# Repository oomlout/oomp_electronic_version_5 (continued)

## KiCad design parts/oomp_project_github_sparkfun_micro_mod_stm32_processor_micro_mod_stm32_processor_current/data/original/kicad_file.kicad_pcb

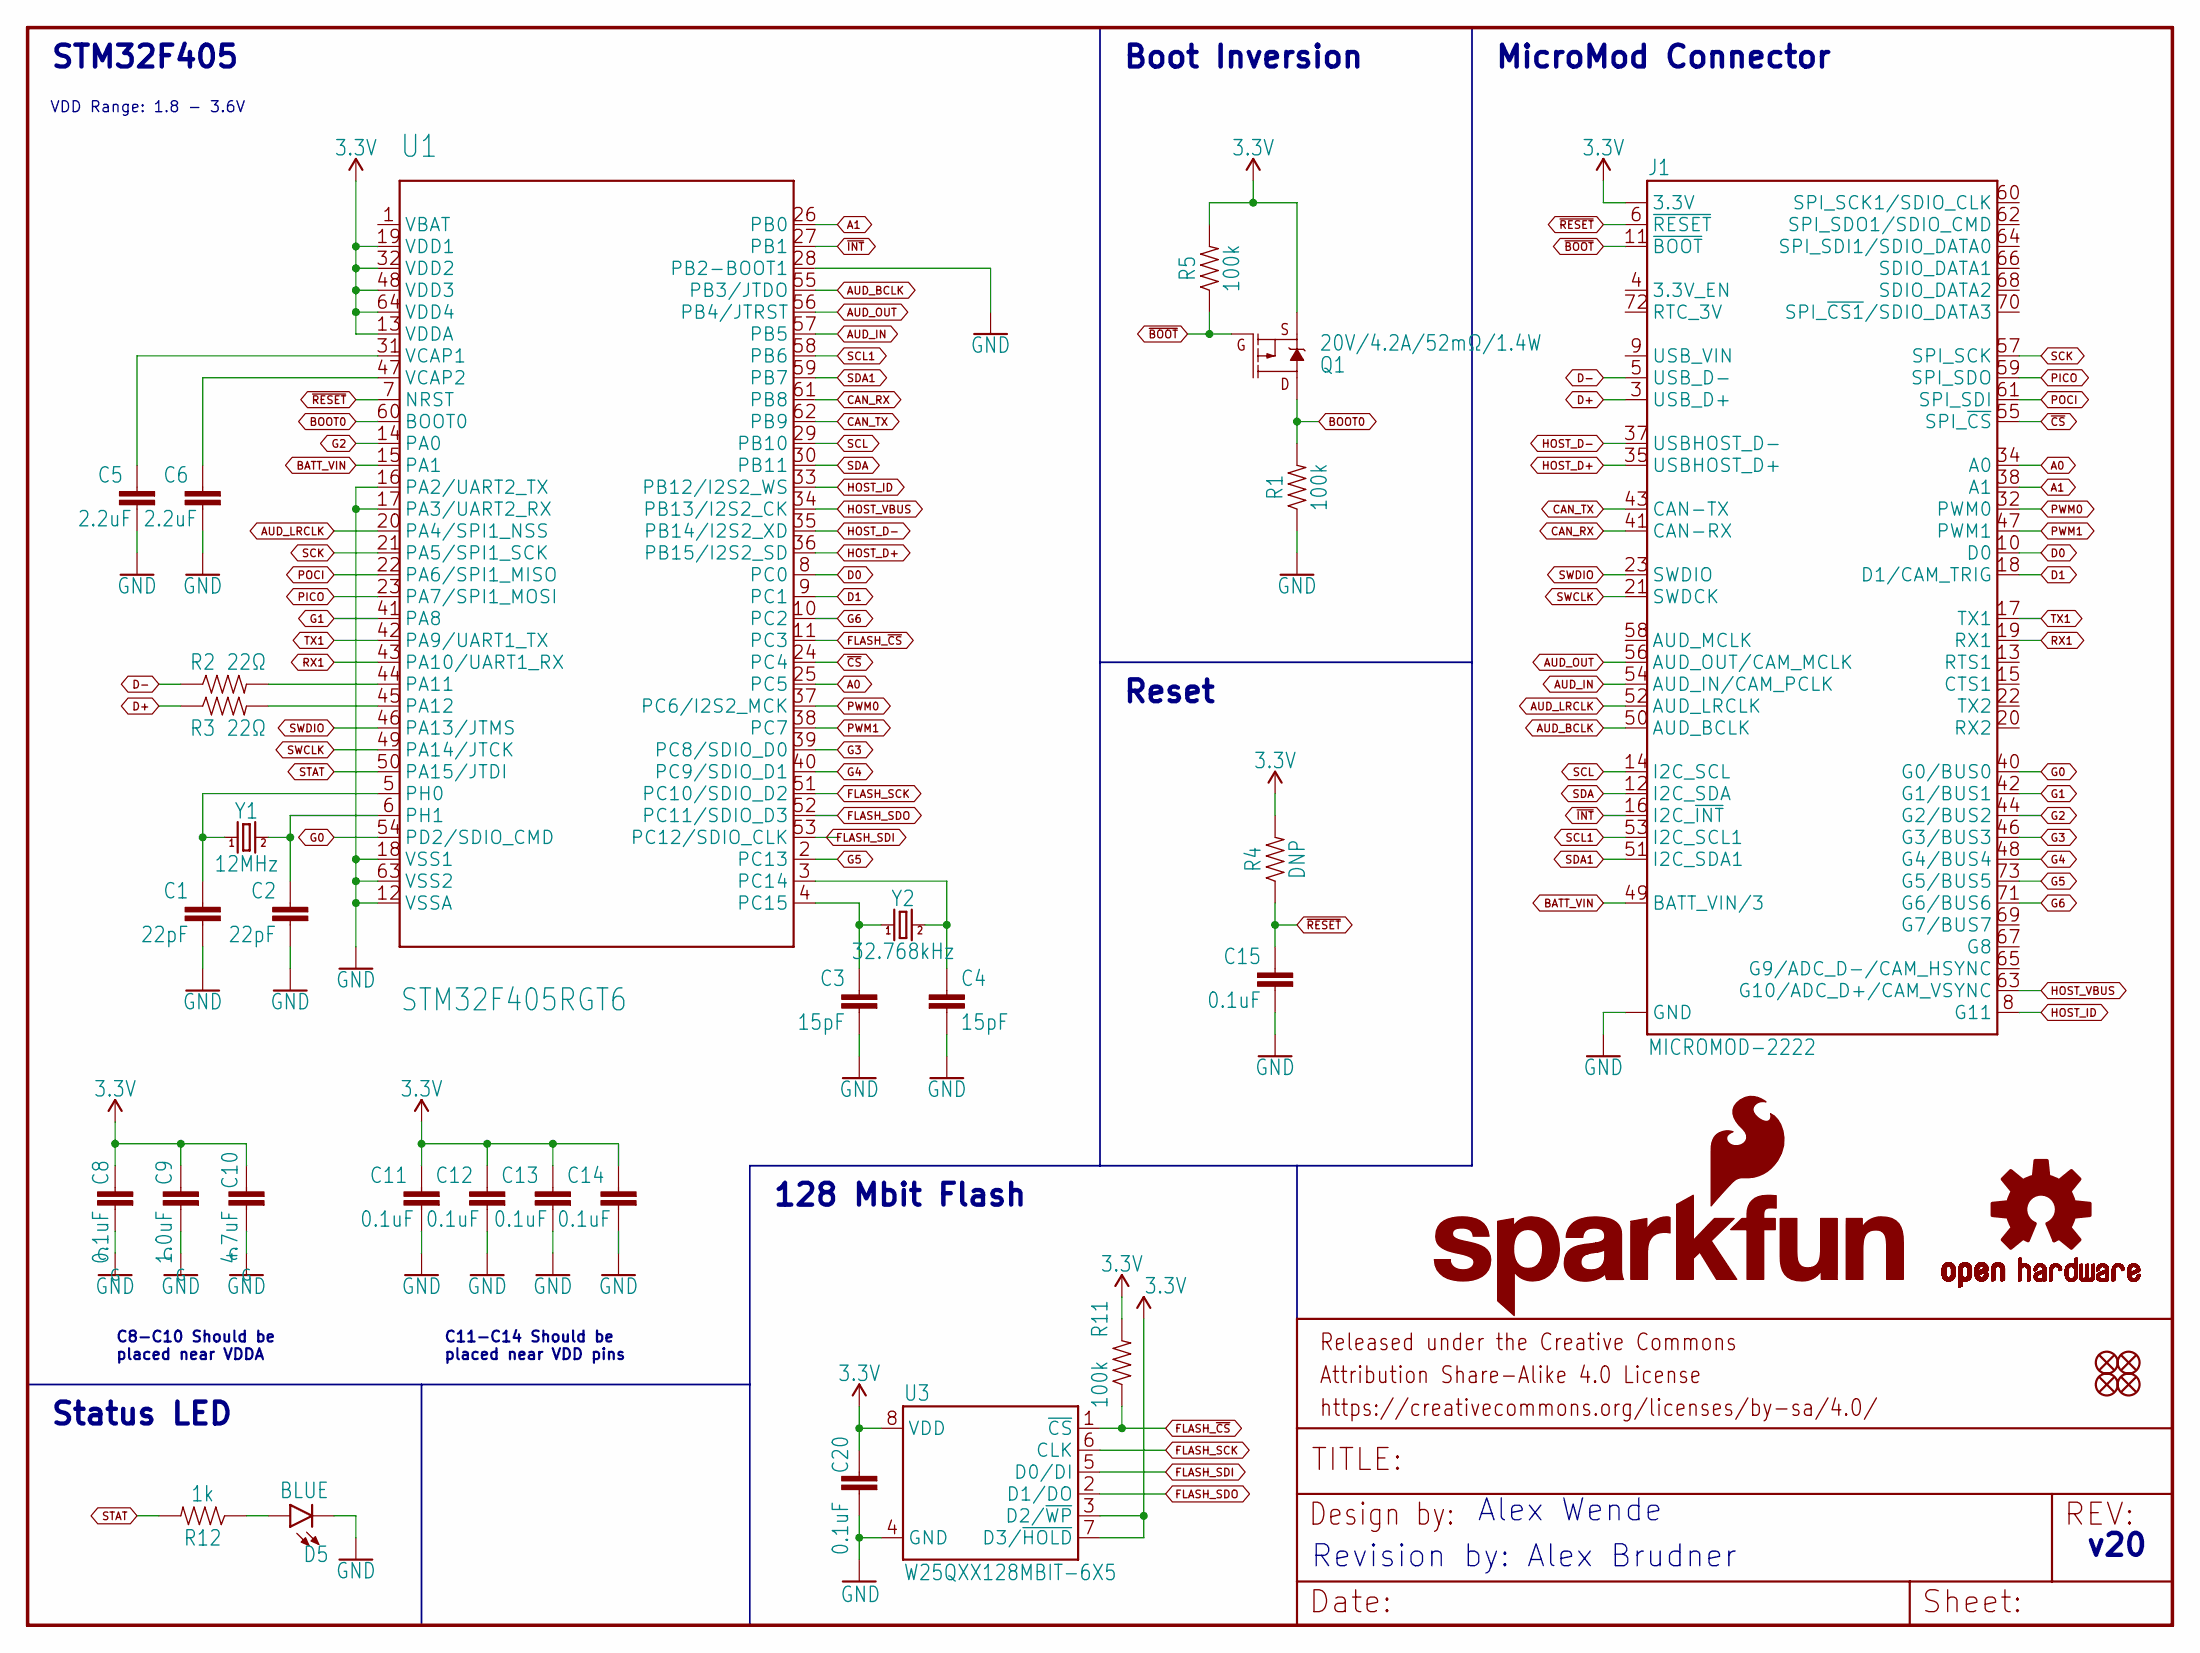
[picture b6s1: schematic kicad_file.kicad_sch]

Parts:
C1, C2: 22pF; 0402-TIGHT
C3, C4: 15pF; 0402-TIGHT
C5, C6: 2.2uF; 0402-TIGHT
C8, C11, C12, C13, C14, C15, C20: 0.1uF; 0402-TIGHT
C9: 1.0uF; 0402-TIGHT
C10: 4.7uF; 0402-TIGHT
D5: BLUE; LED-0603
FD1, FD2, FD3, FD4: FIDUCIALUFIDUCIAL; FIDUCIAL-MICRO
FRAME1: FRAME-LETTER; CREATIVE_COMMONS
J1: MICROMOD-2222; M.2-CARD-E-22
LOGO2: OSHW-LOGOS; OSHW-LOGO-S
LOGO3: SFE_LOGO_NAME_FLAME.1_INCH; SFE_LOGO_NAME_FLAME_.1
Q1: 20V/4.2A/52mΩ/1.4W; SOT23-3
R1, R5, R11: 100k; 0402-TIGHT
R2, R3: 22Ω; 0402-TIGHT
R4: DNP; 0402-TIGHT_NO_CREAM
R12: 1k; 0402-TIGHT
U1: STM32F405RGT6; TQFP64
U3: W25QXX128MBIT-6X5; WSON-8-6X5
Y1: 12MHz; CRYSTAL-SMD-5X3.2-4PAD
Y2: 32.768kHz; CRYSTAL-SMD-3.2X1.5MM

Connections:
3.3V: C8.1, C9.1, C10.1, C11.1, C12.1, C13.1, C14.1, C20.1, J1.2 (3.3V), J1.74 (3.3V), Q1.2 (S), R4.2, R5.2, R11.2, U1.13 (VDDA), U1.19 (VDD1), U1.32 (VDD2), U1.48 (VDD3), U1.64 (VDD4), U3.3 (D2/~WP), U3.7 (D3/~HOLD), U3.8 (VDD)
A0: J1.34 (A0), U1.25 (PC5)
A1: J1.38 (A1), U1.26 (PB0)
AUD_BCLK: J1.50 (AUD_BCLK), U1.55 (PB3/JTDO)
AUD_IN: J1.54 (AUD_IN/CAM_PCLK), U1.57 (PB5)
AUD_LRCLK: J1.52 (AUD_LRCLK), U1.20 (PA4/SPI1_NSS)
AUD_OUT: J1.56 (AUD_OUT/CAM_MCLK), U1.56 (PB4/JTRST)
BATT_VIN: J1.49 (BATT_VIN/3), U1.15 (PA1)
BOOT0: Q1.3 (D), R1.2, U1.60 (BOOT0)
CAN_RX: J1.41 (CAN-RX), U1.61 (PB8)
CAN_TX: J1.43 (CAN-TX), U1.62 (PB9)
D0: J1.10 (D0), U1.8 (PC0)
D1: J1.18 (D1/CAM_TRIG), U1.9 (PC1)
D+: J1.3 (USB_D+), R3.1
D-: J1.5 (USB_D-), R2.1
FLASH_SCK: U1.51 (PC10/SDIO_D2), U3.6 (CLK)
FLASH_SDI: U1.53 (PC12/SDIO_CLK), U3.5 (D0/DI)
FLASH_SDO: U1.52 (PC11/SDIO_D3), U3.2 (D1/DO)
FLASH_~CS: R11.1, U1.11 (PC3), U3.1 (~CS)
G0: J1.40 (G0/BUS0), U1.54 (PD2/SDIO_CMD)
G1: J1.42 (G1/BUS1), U1.41 (PA8)
G2: J1.44 (G2/BUS2), U1.14 (PA0)
G3: J1.46 (G3/BUS3), U1.39 (PC8/SDIO_D0)
G4: J1.48 (G4/BUS4), U1.40 (PC9/SDIO_D1)
G5: J1.73 (G5/BUS5), U1.2 (PC13)
G6: J1.71 (G6/BUS6), U1.10 (PC2)
GND: C1.2, C2.2, C3.2, C4.2, C5.2, C6.2, C8.2, C9.2, C10.2, C11.2, C12.2, C13.2, C14.2, C15.2, C20.2, D5.C, J1.1 (GND), J1.7 (GND), J1.33 (GND), J1.36 (GND), J1.39 (GND), J1.45 (GND), J1.75 (GND), J1.GND1 (GND), J1.GND2 (GND), J1.GND3 (GND), R1.1, U1.12 (VSSA), U1.16 (PA2/UART2_TX), U1.17 (PA3/UART2_RX), U1.18 (VSS1), U1.28 (PB2-BOOT1), U1.63 (VSS2), U3.4 (GND)
HOST_D+: J1.35 (USBHOST_D+), U1.36 (PB15/I2S2_SD)
HOST_D-: J1.37 (USBHOST_D-), U1.35 (PB14/I2S2_XD)
HOST_ID: J1.8 (G11), U1.33 (PB12/I2S2_WS)
HOST_VBUS: J1.63 (G10/ADC_D+/CAM_VSYNC), U1.34 (PB13/I2S2_CK)
unnamed: D5.A, R12.1
unnamed: R2.2, U1.44 (PA11)
unnamed: R3.2, U1.45 (PA12)
unnamed: C4.1, U1.3 (PC14), Y2.P$2 (2)
unnamed: C3.1, U1.4 (PC15), Y2.P$1 (1)
unnamed: C2.1, U1.6 (PH1), Y1.3 (2)
unnamed: C1.1, U1.5 (PH0), Y1.1
unnamed: C6.1, U1.47 (VCAP2)
unnamed: C5.1, U1.31 (VCAP1)
PICO: J1.59 (SPI_SDO), U1.23 (PA7/SPI1_MOSI)
POCI: J1.61 (SPI_SDI), U1.22 (PA6/SPI1_MISO)
PWM0: J1.32 (PWM0), U1.37 (PC6/I2S2_MCK)
PWM1: J1.47 (PWM1), U1.38 (PC7)
RX1: J1.19 (RX1), U1.43 (PA10/UART1_RX)
SCK: J1.57 (SPI_SCK), U1.21 (PA5/SPI1_SCK)
SCL: J1.14 (I2C_SCL), U1.29 (PB10)
SCL1: J1.53 (I2C_SCL1), U1.58 (PB6)
SDA: J1.12 (I2C_SDA), U1.30 (PB11)
SDA1: J1.51 (I2C_SDA1), U1.59 (PB7)
STAT: R12.2, U1.50 (PA15/JTDI)
SWCLK: J1.21 (SWDCK), U1.49 (PA14/JTCK)
SWDIO: J1.23 (SWDIO), U1.46 (PA13/JTMS)
TX1: J1.17 (TX1), U1.42 (PA9/UART1_TX)
~BOOT: J1.11 (~BOOT), Q1.1 (G), R5.1
~CS: J1.55 (SPI_~CS), U1.24 (PC4)
~INT: J1.16 (I2C_~INT), U1.27 (PB1)
~RESET: C15.1, J1.6 (~RESET), R4.1, U1.7 (NRST)

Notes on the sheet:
C8-C10 Should be placed near VDDA
Reset
Status LED
128 Mbit Flash
C11-C14 Should be placed near VDD pins
VDD Range: 1.8 - 3.6V
v20
Revision by: Alex Brudner
STM32F405
Boot Inversion
MicroMod Connector
Alex Wende

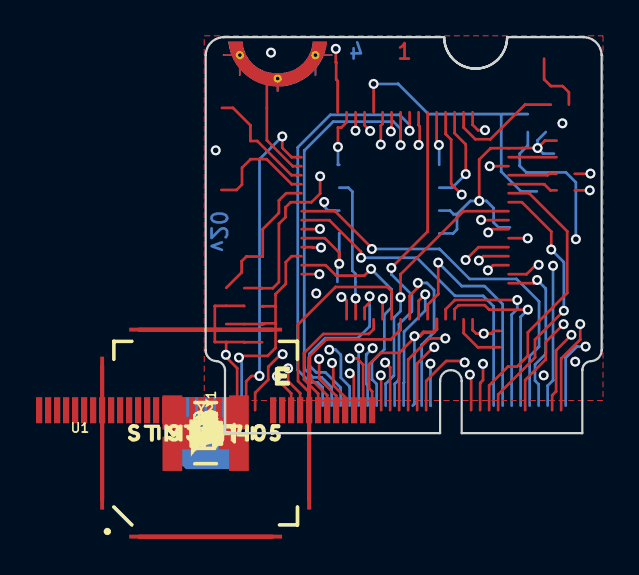
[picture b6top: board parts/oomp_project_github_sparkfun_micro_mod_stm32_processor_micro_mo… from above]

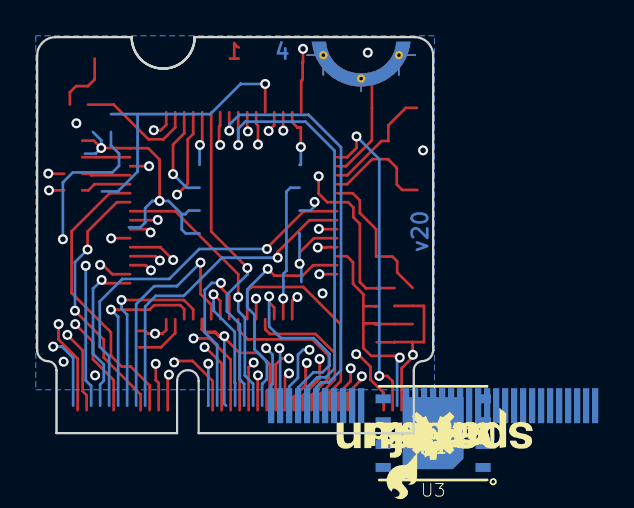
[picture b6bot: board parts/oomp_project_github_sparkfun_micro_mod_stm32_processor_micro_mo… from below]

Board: 4 copper layers, 22.0 x 22.0 mm, 43 parts (12 on the bottom side), 58 nets.

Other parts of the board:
U$1: STAT0
U$2: STM320
U$3: MICROMOD_MI_LOGO_.35
U$4: STM32F4050
U$5: MICROMOD_LOGO_.3
U$6: SFE_LOGO_FLAME_.1
U$7: PRODUCTION_INSTRUCTIONS

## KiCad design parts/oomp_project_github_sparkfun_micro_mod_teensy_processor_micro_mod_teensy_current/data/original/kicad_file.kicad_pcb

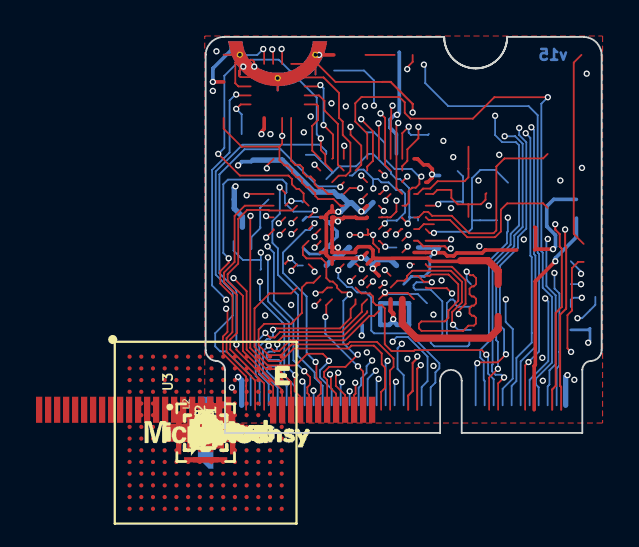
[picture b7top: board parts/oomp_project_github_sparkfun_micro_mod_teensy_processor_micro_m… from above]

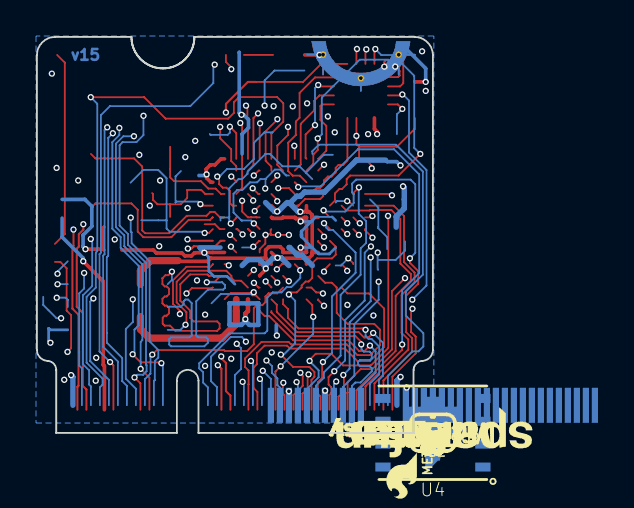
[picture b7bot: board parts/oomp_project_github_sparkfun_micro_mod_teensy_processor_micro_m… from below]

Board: 4 copper layers, 22.0 x 22.0 mm, 82 parts (52 on the bottom side), 95 nets.

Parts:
C1, C11: 2.2uF; 0402-TIGHT
C2, C14, C18, C26, C27: 4.7uF; 0402-TIGHT
C3, C4, C12, C13, C15, C17, C20, C22, C23, C24, C25, C28, C29: 0.22uF; 0402-TIGHT
C5, C16: 10nF; 0402-TIGHT
C6, C7: 12pF; 0402-TIGHT
C8, C9: 20pF; 0402-TIGHT
C10, C19, C21: 10uF; 0402-TIGHT
D1: BLUE; LED-0603
D2, D3, D4: 120mA/40V/370mV; SOD-523
D5: Yellow; LED-0603
FB1, FB2: 120Ω; 0402-TIGHT
FD1, FD2, FD3, FD4: FIDUCIALUFIDUCIAL; FIDUCIAL-MICRO
FRAME1: FRAME-LEDGER; CREATIVE_COMMONS
J1: MICROMOD-2222; M.2-CARD-E-22
L2: 4.7μH; 1008(2520)
LOGO1: SFE_LOGO_NAME_FLAME.1_INCH; SFE_LOGO_NAME_FLAME_.1
LOGO2: OSHW-LOGONO_SILK; DUMMY
LOGO3: SPECIAL_INSTRUCTIONS-ORDERING; ORDERING_INSTRUCTIONS
MEAS0: SMT-JUMPER_2_NC_TRACE_SILK
Q1: 20V/4.2A/52mΩ/1.4W; SOT23-3
Q2: 20V/0.2A/8MHz/1.2Ω/1Vth; SOT-416FL
R1, R7: 1k; 0402-TIGHT
R2, R5, R6: 100k; 0402-TIGHT
R4: 2.2M; 0402-TIGHT
TP1, TP2, TP3, TP4, TP5, TP6, TP7, TP8, TP9, TP10, TP11, TP12, TP13: PAD.03X.03
U1: IMXRT1062DV10X10; IMXRT1062
U3: MKL02Z32VFG4; QFN-16
U4: W25QXX128MBIT-6X5; WSON-8-6X5-SKINNY_CENTERPAD
U$1, U$3: TEENSY2
U$4: MICROMOD_MI_LOGO_.35
U$6: SFE_LOGO_FLAME_.1
U$7, U$11: MICROMOD_LOGO_.3
U$8: MEAS2
U$9: PROG0
U$10: STAT1
Y1: 32.768kHz; CRYSTAL-SMD-3.2X1.5MM
Y2: 24MHz; CRYSTAL-SMD-2.0X1.6MM

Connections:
3.3V: D2.A, J1.2, J1.74, Q1.2, R2.1, TP13.P$1
3.3V_CONTROLLED: C1.1, C2.1, C3.1, C4.1, C5.1, C28.1, C29.1, D5.A, FB2.1, Q1.3, R6.1, TP12.P$1, U1.E6, U1.E9, U1.F5, U1.F10, U1.J6, U1.J10, U1.K4, U1.K5, U1.N14, U1.P12, U3.1, U4.8
24MHZ_1: C7.1, U1.N11, Y2.3
24MHZ_2: C6.1, R4.2, U1.P11, Y2.1
32KHZ_1: C8.1, U1.N9, Y1.P$1
32KHZ_2: C9.1, U1.P9, Y1.P$2
32KHZ_TEST: TP1.P$1, U1.M14
34/DAT1: J1.66, U1.K1
35/DAT0: J1.64, U1.J1
36/CLK: J1.60, U1.J3
37/CMD: J1.62, U1.J4
38/DAT3: J1.70, U1.J2
39/DAT2: J1.68, U1.H2
A0/14: J1.34, U1.L11
A1/15: J1.38, U1.M12
AUD_IN/8: J1.54, U1.A11
AUD_OUT/7: J1.56, U1.B11
BATT_VIN/22/A8: J1.49, U1.H13
BCLK/21/A7: J1.50, U1.J13
BOOTMODE0: U1.F11, U3.4
CAN_RX/30: J1.41, U1.E4
CAN_TX/31: J1.43, U1.C3
CIPO/12: J1.61, U1.E7
COPI/11: J1.59, U1.E8
CS/10: J1.55, U1.D7
D0/4: J1.10, U1.H5
D1/5: J1.18, U1.H3
DCDC_IN: C10.1, C14.1, C15.1, FB2.2, U1.L1, U1.L2
DCDC_LP: L2.1, U1.M1, U1.M2
DEBUG_EN: U1.F3, U3.15
DEBUG_SWO: U1.D10, U3.12
GND: C1.2, C2.2, C3.2, C4.2, C5.2, C6.2, C7.2, C8.2, C9.2, C10.2, C11.2, C12.2, C13.2, C14.2, C15.2, C16.2, C17.2, C18.2, C19.2, C20.2, C21.2, C22.2, C23.2, C24.2, C25.2, C26.2, C27.2, C28.2, C29.2, D1.C, J1.1, J1.7, J1.33, J1.36, J1.39, J1.45, J1.75, J1.GND1, J1.GND2, J1.GND3, Q2.2, R4.1, R5.1, U1.A1, U1.A14, U1.B5, U1.B10, U1.E2, U1.E13, U1.G7, U1.G8, U1.G14, U1.H7, U1.H8, U1.J7, U1.J8, U1.K2, U1.K6, U1.K9, U1.K13, U1.L9, U1.N1, U1.N2, U1.N5, U1.N8, U1.P1, U1.P14, U3.2, U3.17, U4.4
GPIO/6: J1.71, U1.D9
GPIO/9: J1.69, U1.A10
GPIO/26/A12: J1.67, U1.G12
GPIO/27/A13: J1.8, U1.J14
GPIO/28/3.3V_EN: J1.4, U1.D5
GPIO/32: J1.65, U1.C10
GPIO/33: J1.63, U1.H4
GPIO/40: J1.40, U1.C8
GPIO/41: J1.42, U1.B8
GPIO/42: J1.44, U1.A8
GPIO/43: J1.46, U1.A9
GPIO/44: J1.48, U1.B9
GPIO/45: J1.73, U1.C9
I2C_~INT/29: J1.16, U1.C5
JTAG_MOD: U1.F13, U3.13
JTAG_TCK: U1.F12, U3.8
JTAG_TDI: U1.F14, U3.7
JTAG_TDO: U1.G13, U3.6
JTAG_TMS: U1.E14, U3.5
JTAG_TRST: R5.2, U1.G10, U1.K3, U3.3
LRCLK/20/A6: J1.52, U1.L13
MCLK/23/A9: J1.58, U1.M13
unnamed: D1.A, R1.1
unnamed: Q1.1, Q2.3, R2.2
unnamed: C11.1, FB1.1, MEAS0.2
unnamed: R7.1, U3.11
unnamed: D5.C, R7.2
NVCC_PLL: C24.1, C26.1, TP6.P$1, U1.P10
ON/~OFF: J1.6, U1.M6
PMIC: Q2.1, R6.2, TP2.P$1, U1.K7
PORB_RESET: U1.M7, U3.9
PROGRAM: J1.11, U3.10
PWM0/3: J1.32, U1.G5
PWM1/2: J1.47, U1.F2
QSPI0: U1.P3, U4.5
QSPI1: U1.N4, U4.2
QSPI2: U1.P4, U4.3
QSPI3: U1.P5, U4.7
QSPI-CLK: U1.L4, U4.6
QSPI-CS: U1.L3, U4.1
RX0/0: J1.19, U1.G11
RX1/16/A2: J1.20, U1.K10
SCK/13: J1.57, R1.2, U1.D8
SCL1/24/A10: J1.53, U1.K14
SCL/19/A5: J1.14, U1.J11
SDA1/25/A11: J1.51, U1.L14
SDA/18/A4: J1.12, U1.K11
SWD_CLK: TP9.P$1, U3.14
SWD_DIO: TP8.P$1, U3.16
TX0/1: J1.17, U1.M11
TX1/17/A3: J1.22, U1.J12
USB2_D+: J1.35, U1.P7
USB2_D-: J1.37, U1.N7
USB_D+: J1.3, U1.L8
USB_D-: J1.5, U1.M8
VCC: C12.1, C13.1, FB1.2, TP3.P$1, U1.N6, U1.P6
VDD_HIGH_CAP: C25.1, C27.1, TP7.P$1, U1.P8
VDD_SNVS_CAP: C23.1, TP5.P$1, U1.M10
VDD_SNVS_IN: C22.1, D2.C, D3.C, D4.C, TP4.P$1, U1.M9
VDD_SOC_IN: C16.1, C17.1, C18.1, C19.1, L2.2, TP10.P$1, U1.F6, U1.F7, U1.F8, U1.F9, U1.G6, U1.G9, U1.H6, U1.H9, U1.J5, U1.J9
VDD_USB_CAP: C20.1, C21.1, D4.A, TP11.P$1, U1.K8
V_BATT: D3.A, J1.72
V_USB: J1.9, MEAS0.1
